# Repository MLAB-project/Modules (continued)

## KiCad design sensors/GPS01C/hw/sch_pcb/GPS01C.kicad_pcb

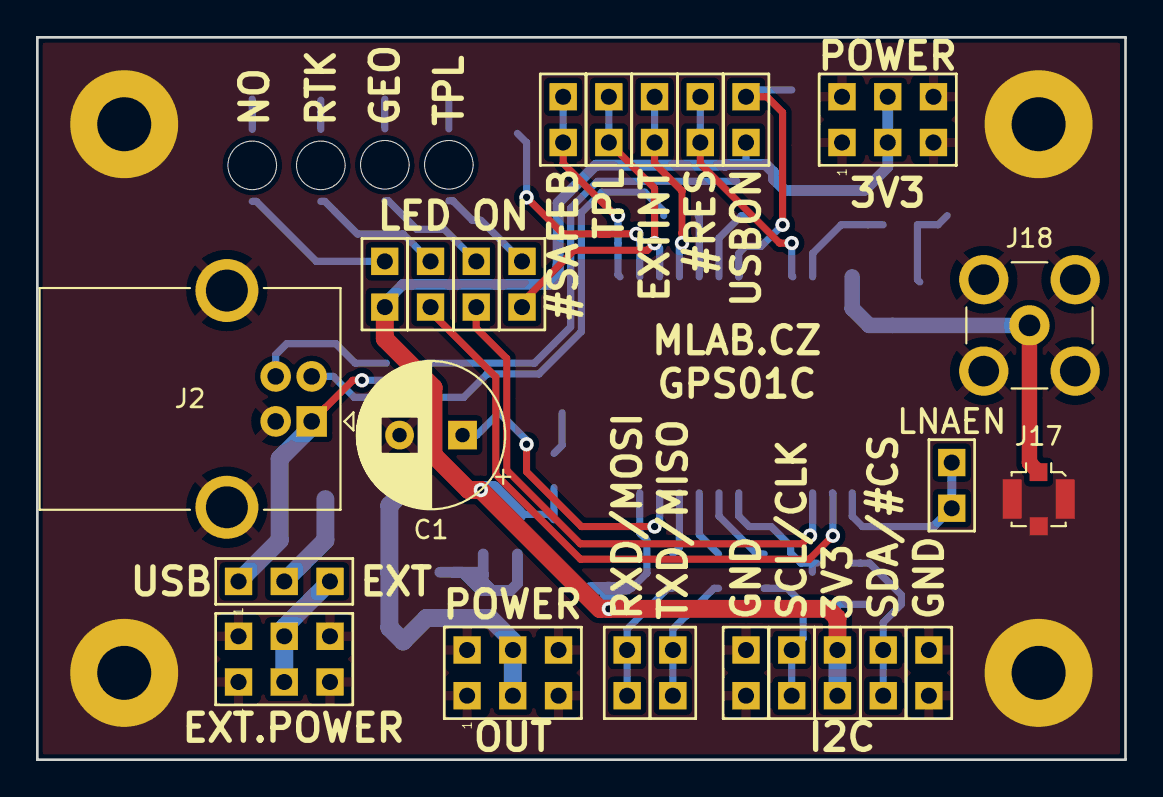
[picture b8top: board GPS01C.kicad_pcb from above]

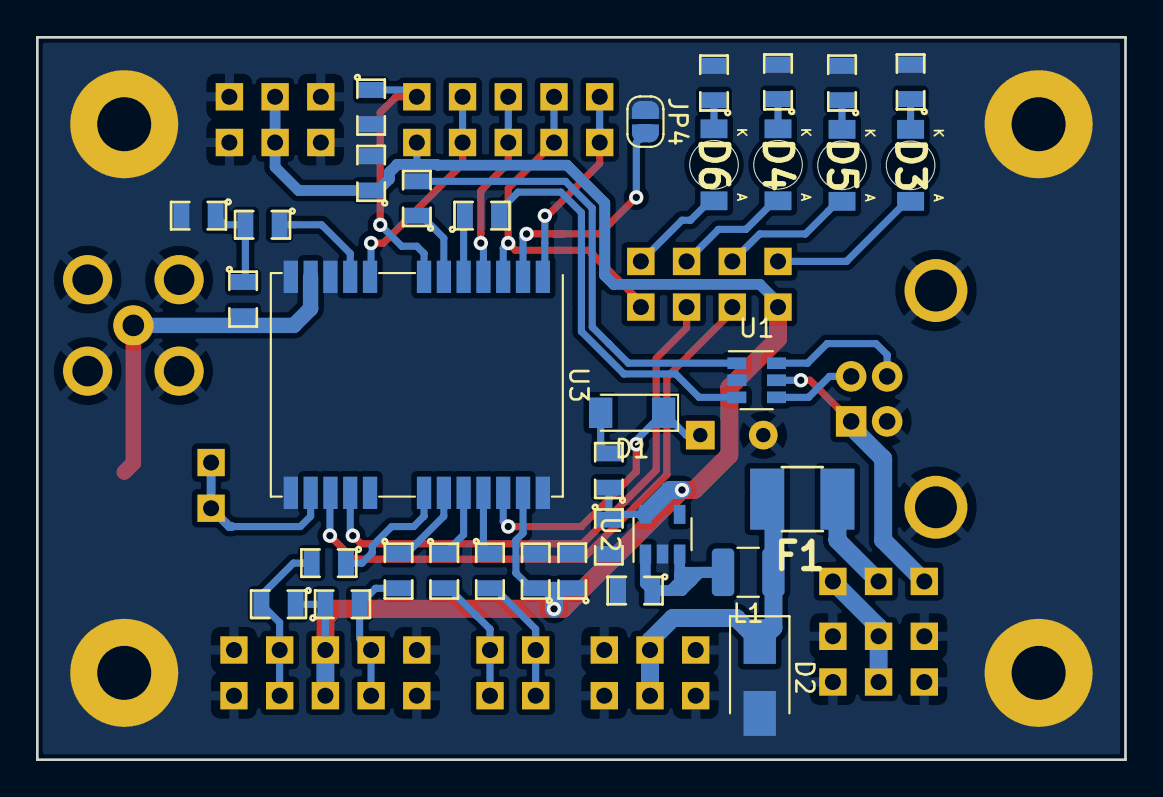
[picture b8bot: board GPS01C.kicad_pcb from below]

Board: 2 copper layers, 60.5 x 40.1 mm, 63 parts (34 on the bottom side), 43 nets.

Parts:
C1: 1F; CP_Radial_D8.0mm_P3.50mm
C2: 10uF; SMD-0805
C3, C5, C6: 1uF; SMD-0805
C4: 100nF; SMD-0805
C7: 10nF; SMD-0805
D1: BZV55C-3,6V; D_MiniMELF
D2: M4; D_SMA
D3: RED; LED_1206
D4, D5: YELLOW; LED_1206
D6: GREEN; LED_1206
F1: 750mA; 1812
J1, J3, J15: HEADER_2x03_PARALLEL; Straight_2x03
J2: USB_B; USB_B_OST_USB-B1HSxx_Horizontal
J4, J5, J6, J7, J8, J9, J10, J11, J12, J13, J14, J16: HEADER_2x01_PARALLEL; Straight_2x01
J17: u.FL; U.FL_Molex_MCRF_73412-0110_Vertical
J18: SMA; SMB_Jack_Vertical
JP1: Jumper_3_Bridged12; Straight_1x03
JP2, JP6: Jumper_2_Bridged; Straight_1x02
JP4: Jumper_2_Open; SolderJumper-2_P1.3mm_Open_RoundedPad1.0x1.5mm
JP7, JP8, JP9: Jumper_2_Open; Straight_1x02
L1: NL322522T-101K; L_1210_3225Metric
L2: 27nH; SMD-0805
M1, M2, M3, M4: HOLE; MountingHole_3mm
R1: 22R; SMD-0805
R2, R3, R15: 10k; SMD-0805
R4, R5, R6, R7, R8, R9: 33R; SMD-0805
R10, R12, R13, R14: 620R; SMD-0805
R11: 10R; SMD-0805
U1: USBLC6-2SC6; SOT-23-6
U2: MIC5504-3.3YM5; SOT-23-5
U3: NEO-M8P; ublox_NEO

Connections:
+3V3: C3.1, C4.1, C5.1, C6.1, J8.1, J8.2, J15.3, J15.4, JP2.2, JP9.1, R1.1, R2.1, R3.1, U2.5, U3.23
/#RESET: J13.1, J13.2, U3.8
/#SAFEB: J12.1, J12.2, U3.1
/D+: J2.3, U1.6
/D-: J2.2, U1.4
/DM: R4.2, U1.3
/DP: R5.2, U1.1
/D_SEL: JP4.2, U3.2
/EXTINT: J11.1, J11.2, U3.4
/GEO_STAT: D4.2, JP8.2
/LNEN: J14.1, J14.2, U3.14
/RTK_STAT: D5.2, JP7.2
/RXD/MOSI: J5.1, J5.2, R7.2
/SCL/CLK: J7.1, J7.2, R3.2, R9.2
/SDA/#CS: J6.1, J6.2, R2.2, R8.2
/TIMEPULSE: D6.2, JP6.2
/TXD/MISO: J4.1, J4.2, R6.2
/VBACKUP: C1.1, D1.1, U3.22
/VBUS: J2.1, JP1.1, U1.5
/VDD_USB: JP2.1, R15.1, U3.7
GND: C1.2, C2.2, C3.2, C4.2, C5.2, C6.2, C7.2, D2.2, J1.1, J1.2, J1.5, J1.6, J2.4, J2.5, J3.1, J3.2, J3.5, J3.6, J9.1, J9.2, J10.1, J10.2, J15.1, J15.2, J15.5, J15.6, J17.2, J18.2, JP4.1, M1.1, M2.1, M3.1, M4.1, R10.2, R12.2, R13.2, R14.2, R15.2, U1.2, U2.2, U3.10, U3.12, U3.13, U3.24
unnamed: C2.1, L1.2, U2.1, U2.3
unnamed: C7.1, L2.1, R11.2
unnamed: D1.2, R1.2
unnamed: D2.1, F1.2, J3.3, J3.4, L1.1
unnamed: D3.1, R10.1
unnamed: D3.2, JP9.2
unnamed: D4.1, R12.1
unnamed: D5.1, R13.1
unnamed: D6.1, R14.1
unnamed: F1.1, JP1.2
unnamed: J1.3, J1.4, JP1.3
unnamed: J16.1, J16.2, JP6.1, U3.3
unnamed: J17.1, J18.1, L2.2, U3.11
unnamed: JP7.1, U3.15
unnamed: JP8.1, U3.16
unnamed: R4.1, U3.5
unnamed: R5.1, U3.6
unnamed: R6.1, U3.20
unnamed: R7.1, U3.21
unnamed: R8.1, U3.18
unnamed: R9.1, U3.19
unnamed: R11.1, U3.9
